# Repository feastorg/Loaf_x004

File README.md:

# x004 Loaf

Four-Slice Loaf/backplane for building a BREAD from compatible Slices.

## Introduction

[Short introduction on the project.]

## Usage

[Explain how to use the project. Include examples and screenshots if applicable.]

## Documentation

Please refer to the [docs](/docs) for more info.

---

<div align="center">
  
</div>

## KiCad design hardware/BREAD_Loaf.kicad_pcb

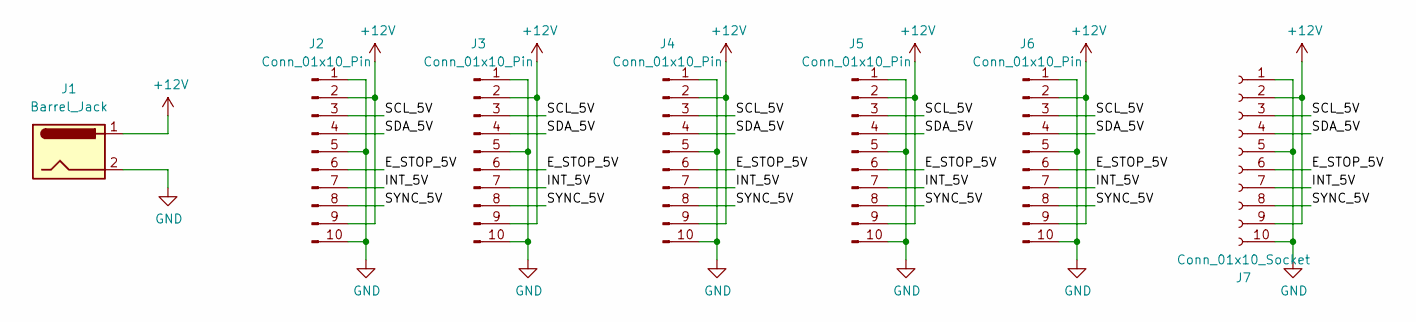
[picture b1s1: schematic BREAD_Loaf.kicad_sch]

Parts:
J1: Barrel_Jack; BarrelJack_CUI_PJ-063AH_Horizontal
J2: Conn_01x10_Pin; PinHeader_1x10_P2.54mm_Horizontal
J3, J4, J5, J6: Conn_01x10_Pin; BREAD_Slice_Bus_10Pin
J7: Conn_01x10_Socket; PinSocket_1x10_P2.54mm_Horizontal

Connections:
+12V: J1.1, J2.2, J2.9, J3.2, J3.9, J4.2, J4.9, J5.2, J5.9, J6.2, J6.9, J7.2, J7.9
/E_STOP_5V: J2.6, J3.6, J4.6, J5.6, J6.6, J7.6
/INT_5V: J2.7, J3.7, J4.7, J5.7, J6.7, J7.7
/SCL_5V: J2.3, J3.3, J4.3, J5.3, J6.3, J7.3
/SDA_5V: J2.4, J3.4, J4.4, J5.4, J6.4, J7.4
/SYNC_5V: J2.8, J3.8, J4.8, J5.8, J6.8, J7.8
GND: J1.2, J2.1, J2.5, J2.10, J3.1, J3.5, J3.10, J4.1, J4.5, J4.10, J5.1, J5.5, J5.10, J6.1, J6.5, J6.10, J7.1, J7.5, J7.10

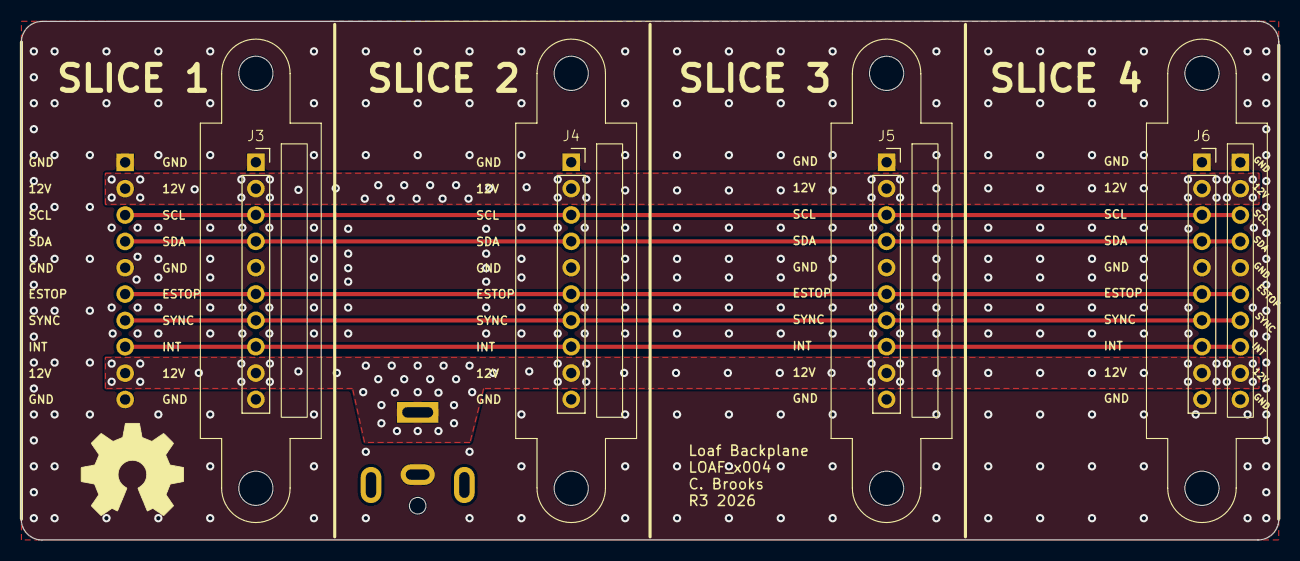
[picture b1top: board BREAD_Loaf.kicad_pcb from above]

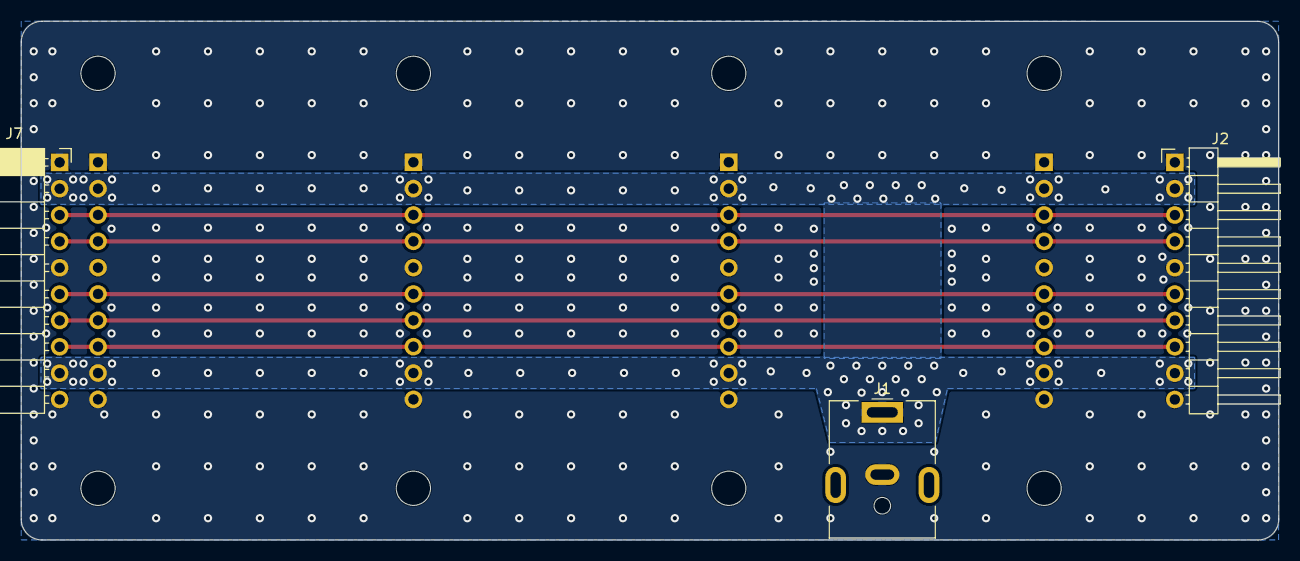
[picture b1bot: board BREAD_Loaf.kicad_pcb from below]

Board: 2 copper layers, 121.2 x 50.0 mm, 8 parts (3 on the bottom side), 7 nets.

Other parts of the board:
Ref**: Val**; OSHW_Logo_10mm

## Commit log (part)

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2026-04-18 chore: minor updates
